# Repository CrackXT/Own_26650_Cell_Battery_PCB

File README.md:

# Own_26650_Cell_Battery_PCB

PCB files for a 26650 cell mount on a separate board

# Description

Compatible with protected 26650 cell type only!

This is an external battery cell board that allows you to mount the appropriate cell holder (26650) and thus have better connection and mounting options in your project or case.

The board can be produced here (AISLER) with the files (.brd and .sch) or by any other PCB manufacturer. -> https://aisler.net/

# Serie

- x

# Layout

Top<br>

Bottom<br>

Routing/Dimensions(inch)<br>

Schematic<br>
Schematic as .pdf at the top of the page.

# License

Open hardware, use it, mod it, whatever you want, feel free...

# Thanks!

Own design and layout.

# Version - Build

v1.1 - 14.01.2022

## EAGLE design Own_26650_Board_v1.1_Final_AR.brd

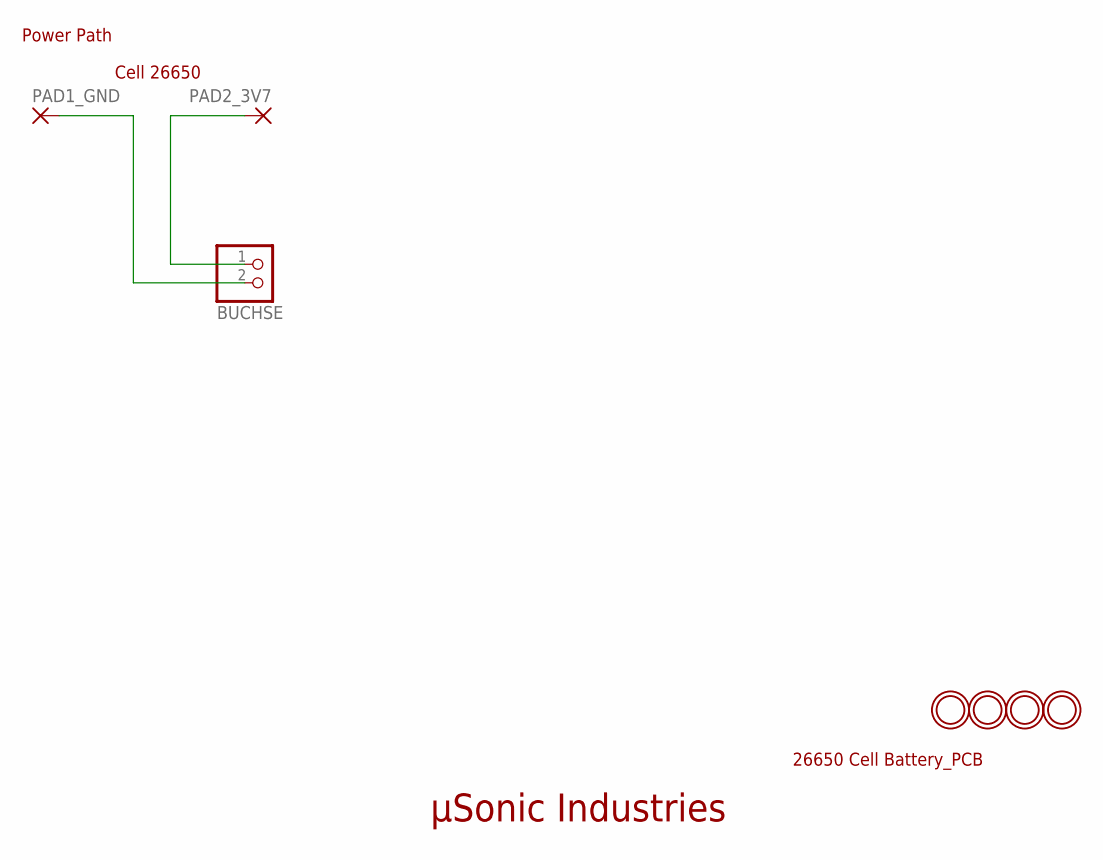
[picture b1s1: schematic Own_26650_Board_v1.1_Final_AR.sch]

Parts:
BUCHSE: JST_2PINOWN; JST-PH-2-THMOWN
PAD1_GND, PAD2_3V7: WIREPADSMDOWN; OWN
U$1, U$2, U$3, U$5: MOUNTINGHOLE2.5; MOUNTINGHOLE_2.5_PLATED

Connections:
3V7: BUCHSE.1 (2), PAD2_3V7.1
GND: BUCHSE.2 (1), PAD1_GND.1

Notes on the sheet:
µSonic Industries
26650 Cell Battery_PCB
Power Path
Cell 26650

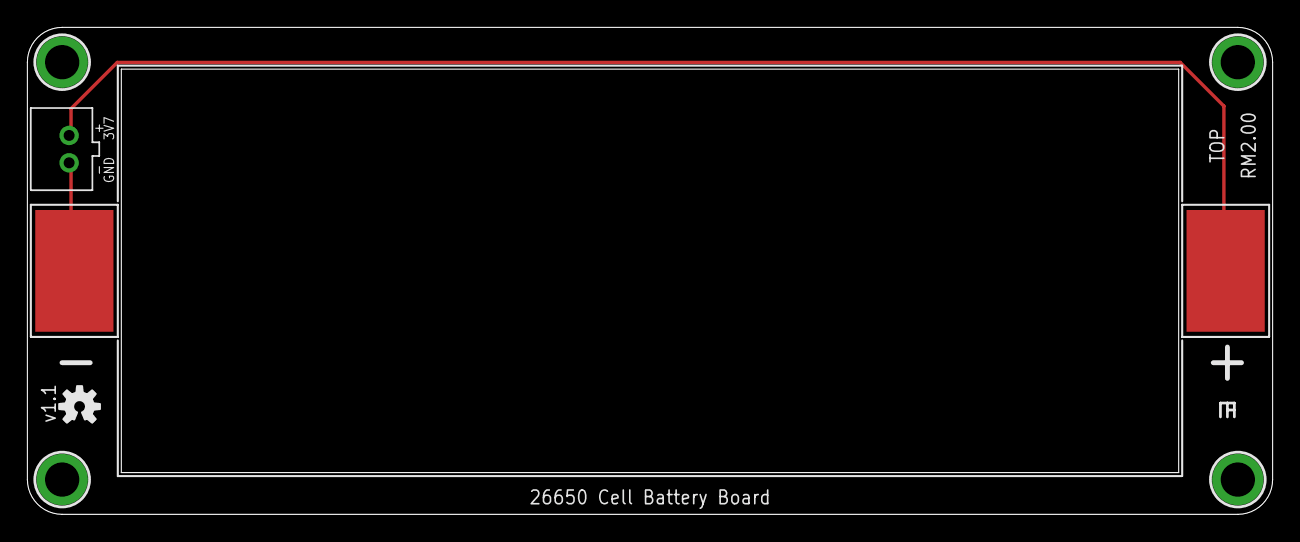
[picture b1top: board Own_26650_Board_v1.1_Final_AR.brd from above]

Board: 2 copper layers, 90.9 x 35.6 mm, 8 parts (0 on the bottom side), 2 nets.

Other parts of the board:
U$4: OSHW-LOGO-S

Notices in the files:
parts and their libraries:
microbuilder: This work is placed in the public domain, and may be freely used for commercial and non-commercial work with the following conditions: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
SparkFun-Aesthetics: Licensing: Creative Commons ShareAlike 4.0 International - https://creativecommons.org/licenses/by-sa/4.0
